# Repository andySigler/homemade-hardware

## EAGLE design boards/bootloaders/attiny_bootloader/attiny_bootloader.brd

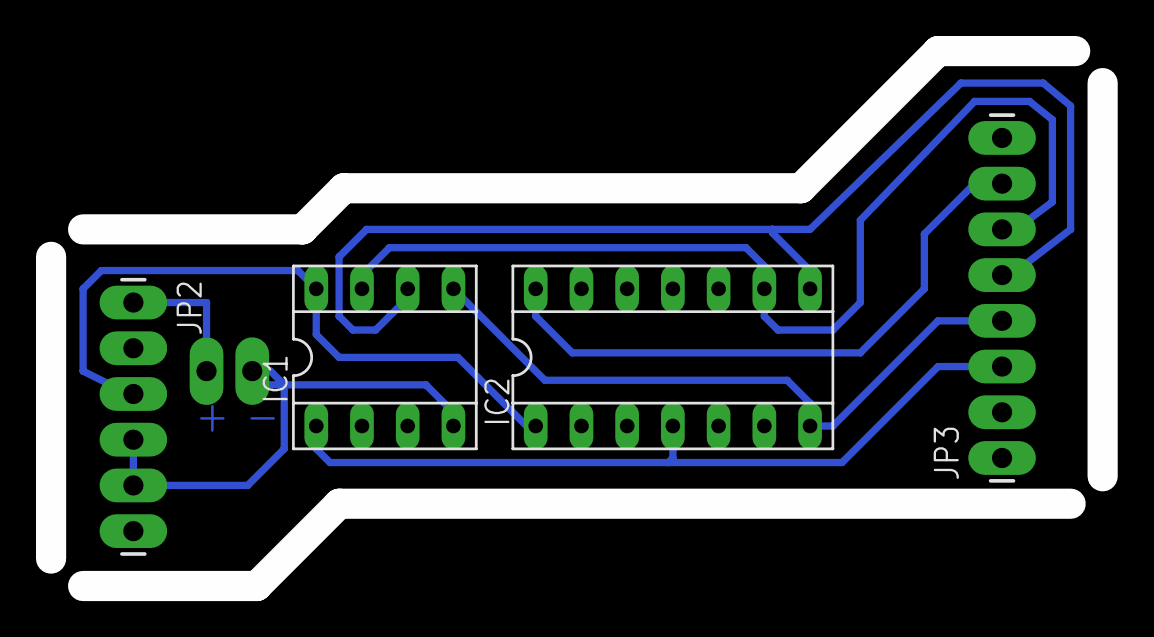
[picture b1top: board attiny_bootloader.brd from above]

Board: 2 copper layers, 58.4 x 29.7 mm, 5 parts (0 on the bottom side), 8 nets.

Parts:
IC1: SOCKET-08
IC2: SOCKET-14
JP1: M02PTH3; 1X02_LONGPADS
JP2: 1X06_LONGPADS
JP3: 1X08_LONGPADS

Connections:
GND: IC1.4, JP1.2, JP2.4, JP2.5
unnamed: IC2.14, JP3.7
unnamed: IC1.1, IC2.4, JP3.3
unnamed: IC1.7, IC2.9, JP3.6
unnamed: IC1.6, IC2.8, JP3.5
unnamed: IC1.5, IC2.7, JP3.4
unnamed: JP1.1, JP2.1
VCC: IC1.8, IC2.1, JP2.3

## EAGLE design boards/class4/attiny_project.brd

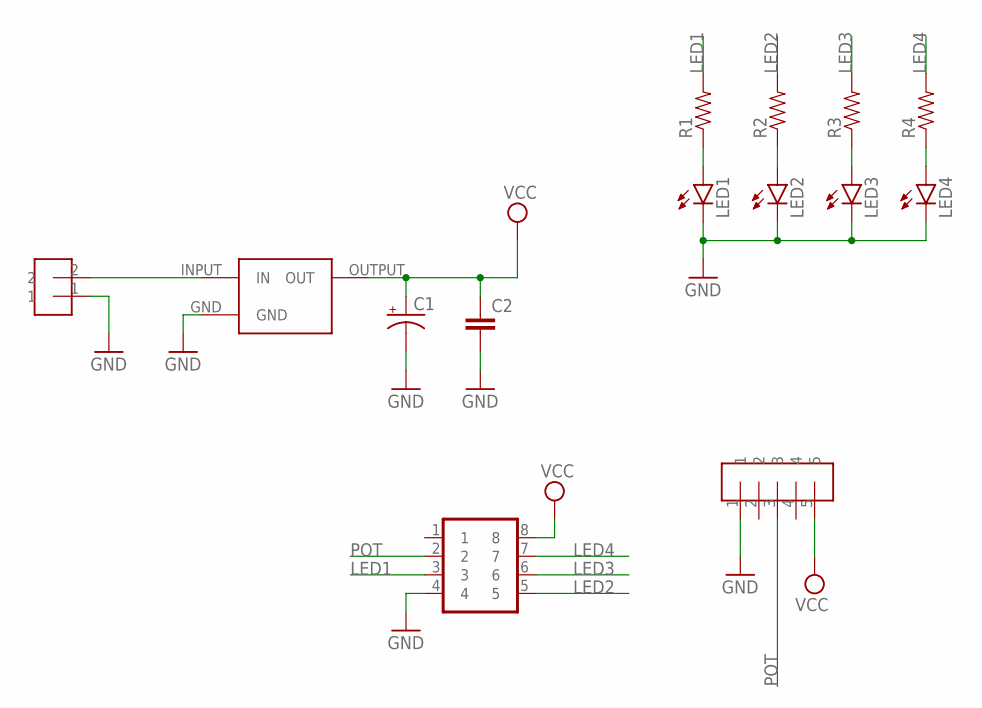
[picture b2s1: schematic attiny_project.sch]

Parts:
C1: CAP_POLPTH2; CPOL-RADIAL-10UF-25V
C2: CAPPTH; CAP-PTH-SMALL
LED1, LED2, LED3, LED4: LED5MM
R1, R2, R3, R4: RESISTORPTH-1/4W; AXIAL-0.4
U$1: SOCKET-8PINDIP; SOCKET-8PIN
U$2: HEADER-5
U$3: REGULATOR5V-MC7805CT; REGULATOR-7805
U$4: HEADER-2

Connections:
GND: C1.2 (-), C2.2, LED1.K (C), LED2.K (C), LED3.K (C), LED4.K (C), U$1.4, U$2.1, U$3.GND, U$4.1
LED1: R1.P$2 (2), U$1.3
LED2: R2.P$2 (2), U$1.5
LED3: R3.P$2 (2), U$1.6
LED4: R4.P$2 (2), U$1.7
unnamed: U$3.INPUT (IN), U$4.2
unnamed: LED1.A, R1.P$1 (1)
unnamed: LED2.A, R2.P$1 (1)
unnamed: LED3.A, R3.P$1 (1)
unnamed: LED4.A, R4.P$1 (1)
POT: U$1.2, U$2.3
VCC: C1.1 (+), C2.1, U$1.8, U$2.5, U$3.OUTPUT (OUT)

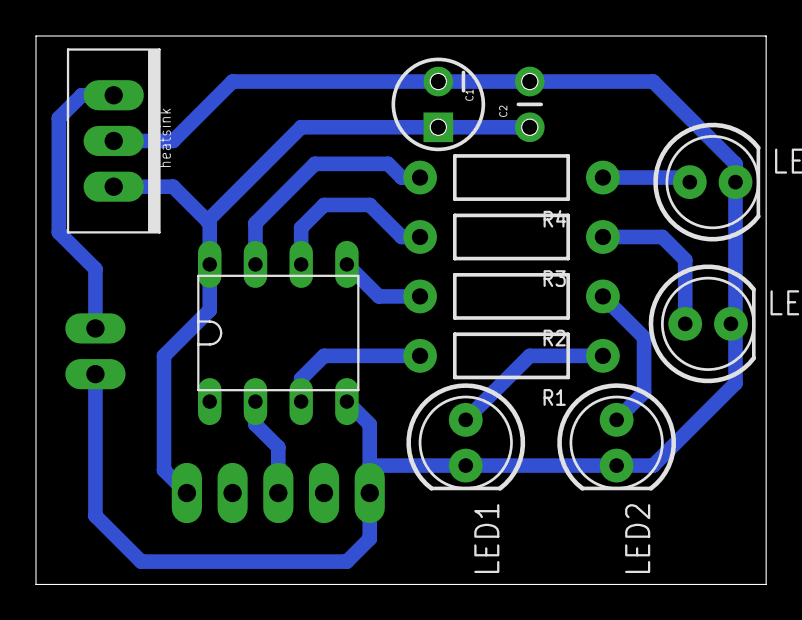
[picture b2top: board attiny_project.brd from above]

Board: 2 copper layers, 40.6 x 30.5 mm, 14 parts (0 on the bottom side), 12 nets.

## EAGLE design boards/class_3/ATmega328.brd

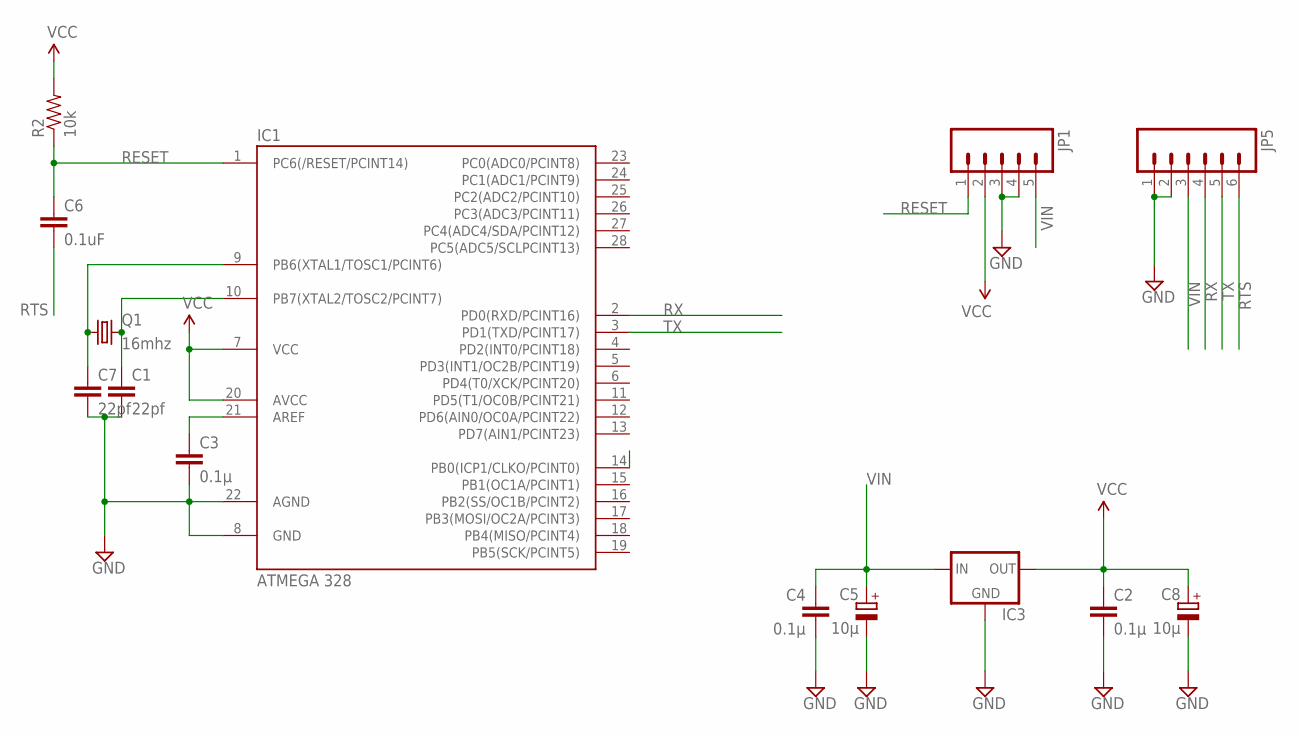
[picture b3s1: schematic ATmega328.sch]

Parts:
C1, C7: 22pf; C025-024X044
C2, C3, C4: 0.1µ; C025-024X044
C5, C8: 10µ; E1,8-4
C6: 0.1uF; CAP-PTH-5MM
IC1: ATMEGA 328; DIL28-3
IC3: V_REG_78XXSIDE; 78XXL
JP1: M05PTH_LONGPADS; 1X05_LONGPADS
JP5: M06NO_SILK; 1X06_NO_SILK
Q1: 16mhz; HC49/S
R2: 10k; 1/6W-RES

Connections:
GND: C1.2, C2.2, C3.2, C4.2, C5.-, C7.2, C8.-, IC1.8 (GND), IC1.22 (AGND), IC3.GND, JP1.3, JP1.4, JP5.1, JP5.2
unnamed: C7.1, IC1.9 (PB6(XTAL1/TOSC1/PCINT6)), Q1.1
unnamed: C3.1, IC1.21 (AREF)
unnamed: C1.1, IC1.10 (PB7(XTAL2/TOSC2/PCINT7)), Q1.2
RESET: C6.1, IC1.1 (PC6(/RESET/PCINT14)), JP1.1, R2.1
RTS: C6.2, JP5.6
RX: IC1.2 (PD0(RXD/PCINT16)), JP5.4
TX: IC1.3 (PD1(TXD/PCINT17)), JP5.5
VCC: C2.1, C8.+, IC1.7 (VCC), IC1.20 (AVCC), IC3.OUT, JP1.2, R2.2
VIN: C4.1, C5.+, IC3.IN, JP1.5, JP5.3

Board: 2 copper layers, 14 parts (0 on the bottom side), 10 nets, no tracks yet.

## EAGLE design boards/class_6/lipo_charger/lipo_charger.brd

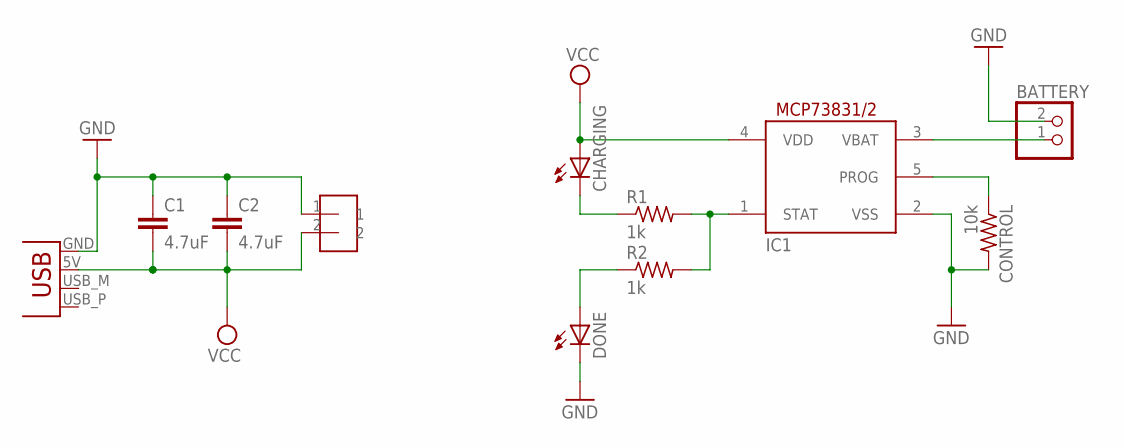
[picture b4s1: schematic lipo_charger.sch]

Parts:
BATTERY: JST_2PIN-SMT-RA; JST-PH-2-SMT-RA
C1, C2: 4.7uF; 0603-CAP
CHARGING: LEDCHIPLED_0603; CHIPLED_0603
CONTROL: 10k; R0603
DONE: LEDCHIPLED_0603; CHIPLED_0603
IC1: MCP73831/OT; SOT23-5L
JP1: USBPCB; USB-A-PCB
R1, R2: 1k; R0603
U$1: HEADER-2

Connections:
GND: BATTERY.2 (1), C1.1, C2.1, CONTROL.2, DONE.C, IC1.2 (VSS), JP1.GND, U$1.1
unnamed: IC1.1 (STAT), R1.2, R2.2
unnamed: CHARGING.C, R1.1
unnamed: DONE.A, R2.1
unnamed: BATTERY.1 (2), IC1.3 (VBAT)
unnamed: CONTROL.1, IC1.5 (PROG)
VCC: C1.2, C2.2, CHARGING.A, IC1.4 (VDD), JP1.5V (VBUS), U$1.2

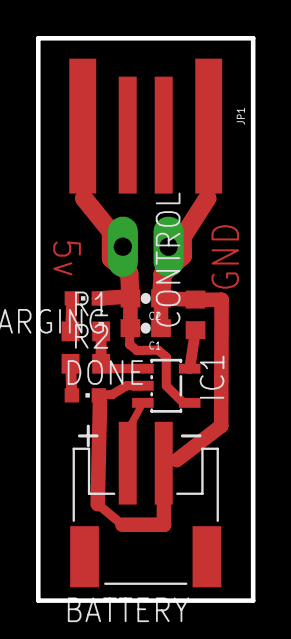
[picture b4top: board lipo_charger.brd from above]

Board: 2 copper layers, 11.9 x 31.2 mm, 11 parts (0 on the bottom side), 7 nets.

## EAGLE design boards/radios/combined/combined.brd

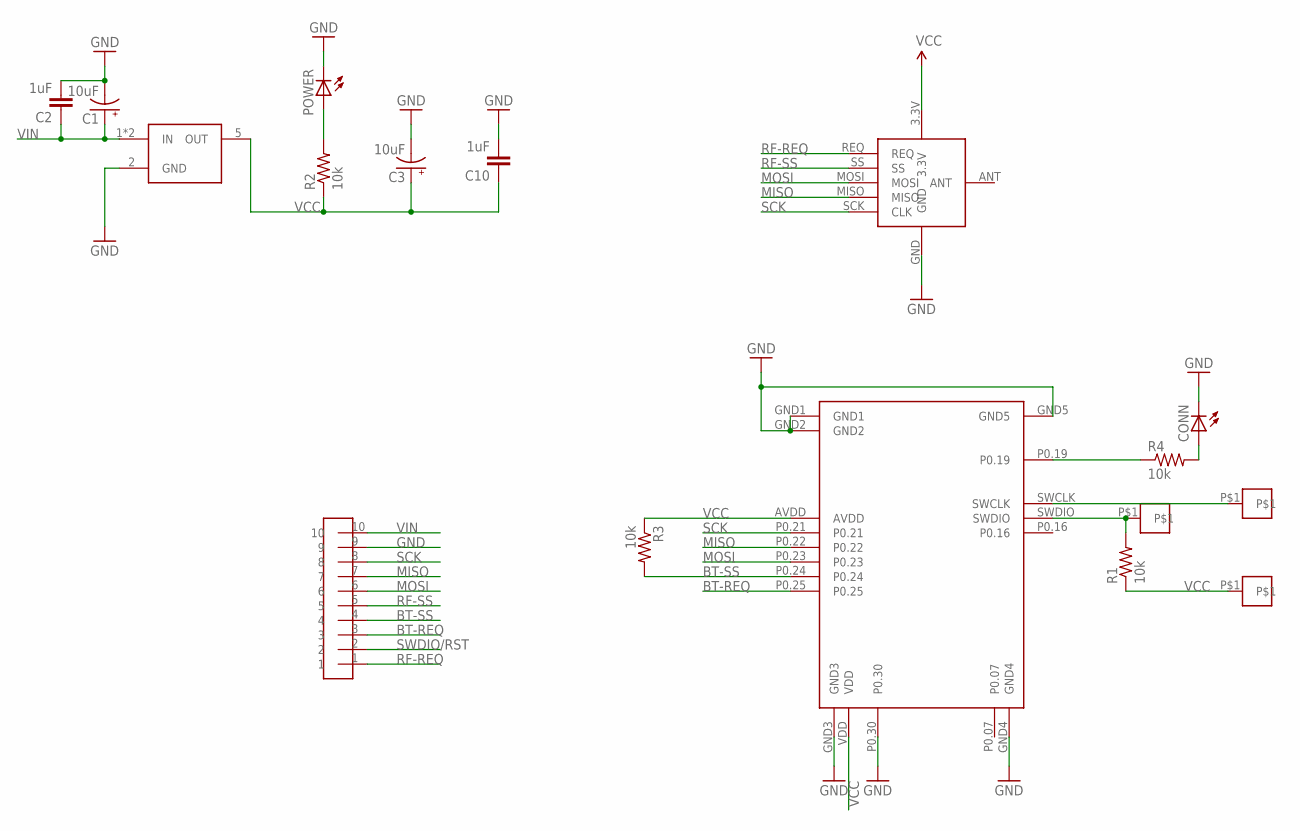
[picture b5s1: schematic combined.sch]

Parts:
C1, C3: 10uF; EIA3216
C2, C10: 1uF; 0603-CAP
CLOCK, CLOCK1: PAD; SMD-ROUND
CONN: LEDCHIP-LED0603; CHIP-LED0603
POWER: LEDCHIP-LED0603; CHIP-LED0603
R1, R3: 10k; 0603-RES
R2, R4: 10k; R0603
U$1: RFM69; S0C-RFM69
U$2: HEADER-10
U$3: REGULATOR3.3V-MIC5205; SOT23-5
U$5: NRF51-MDBT40-SPI; SOC-NRF51-MDBT40-SPI
VCC: PAD; SMD-ROUND

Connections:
BT-REQ: U$2.3, U$5.P0.25
BT-SS: R3.2, U$2.4, U$5.P0.24
GND: C1.C (-), C2.2, C3.C (-), C10.2, CONN.C, POWER.C, U$1.GND, U$2.9, U$3.2 (GND), U$5.GND1, U$5.GND2, U$5.GND3, U$5.GND4, U$5.GND5, U$5.P0.30
MISO: U$1.MISO, U$2.7, U$5.P0.22
MOSI: U$1.MOSI, U$2.6, U$5.P0.23
unnamed: POWER.A, R2.2
unnamed: R4.1, U$5.P0.19
unnamed: CONN.A, R4.2
unnamed: CLOCK.P$1, U$5.SWCLK
RF-REQ: U$1.REQ, U$2.1
RF-SS: U$1.SS, U$2.5
SCK: U$1.SCK (CLK), U$2.8, U$5.P0.21
SWDIO/RST: CLOCK1.P$1, R1.2, U$2.2, U$5.SWDIO
VCC: C3.A (+), C10.1, R1.1, R2.1, R3.1, U$1.3.3V, U$3.5 (OUT), U$5.AVDD, U$5.VDD, VCC.P$1
VIN: C1.A (+), C2.1, U$2.10, U$3.1 (IN), U$3.3 (IN)

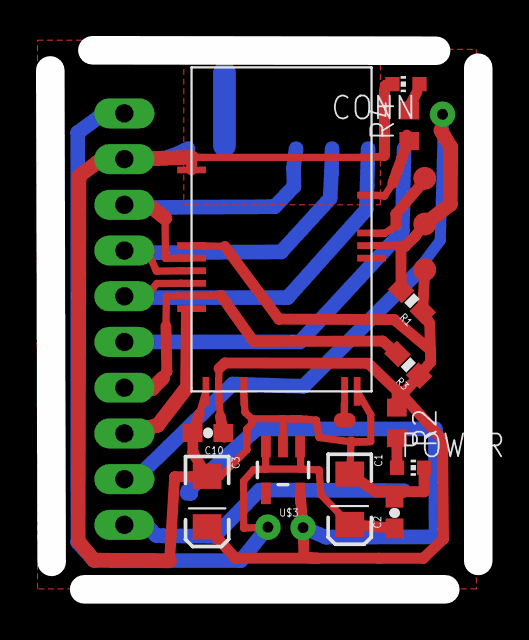
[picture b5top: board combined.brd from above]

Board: 2 copper layers, 23.8 x 29.9 mm, 17 parts (1 on the bottom side), 15 nets.

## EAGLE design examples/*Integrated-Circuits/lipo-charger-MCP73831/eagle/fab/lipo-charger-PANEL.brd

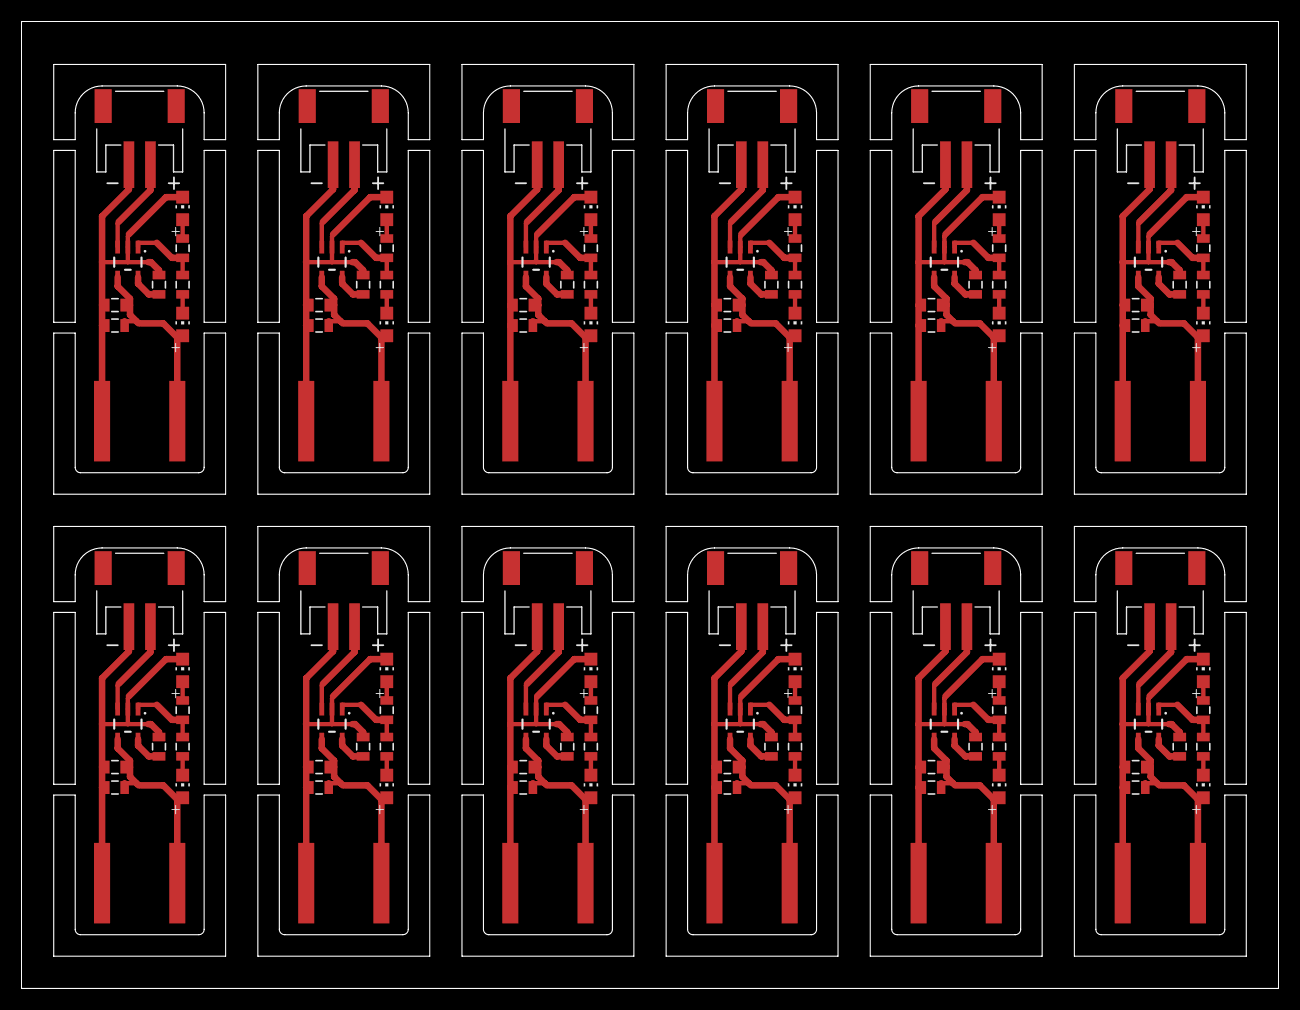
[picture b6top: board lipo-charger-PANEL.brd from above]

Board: 2 copper layers, 117.0 x 90.0 mm, 120 parts (0 on the bottom side), 84 nets.

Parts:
C1, C3, C5, C7, C9, C11, C13, C15, C17, C19, C21, C23: 10uF; 0805
C2, C4, C6, C8, C10, C12, C14, C16, C18, C20, C22, C24: 0.1uF; 0805
IC1, IC2, IC3, IC4, IC5, IC6, IC7, IC8, IC9, IC10, IC11, IC12: IC_LIPO_CHARGER; SOT23-5
LED1, LED3, LED5, LED7, LED9, LED11, LED13, LED15, LED17, LED19, LED21, LED23: Red; CHIP-LED0805
LED2, LED4, LED6, LED8, LED10, LED12, LED14, LED16, LED18, LED20, LED22, LED24: Blue; CHIP-LED0805
R1, R2, R4, R5, R7, R8, R10, R11, R13, R14, R16, R17, R19, R20, R22, R23, R25, R26, R28, R29, R31, R32, R34, R35: 1k; 0805
R3, R6, R9, R12, R15, R18, R21, R24, R27, R30, R33, R36: 10k; 0805
U$1, U$3, U$5, U$7, U$9, U$11, U$13, U$15, U$17, U$19, U$21, U$23: CONN_BATTERY-LIPO-HORIZ; JST-PH-2-SMT-RA
U$2, U$4, U$6, U$8, U$10, U$12, U$14, U$16, U$18, U$20, U$22, U$24: CONN_USB_PCB_POWER; USB-PCB-POWER

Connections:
5V1: C1.1, C2.1, IC1.4, LED1.A, U$2.5V
5V2: C3.1, C4.1, IC2.4, LED3.A, U$4.5V
5V3: C5.1, C6.1, IC3.4, LED5.A, U$6.5V
5V4: C7.1, C8.1, IC4.4, LED7.A, U$8.5V
5V5: C9.1, C10.1, IC5.4, LED9.A, U$10.5V
5V6: C11.1, C12.1, IC6.4, LED11.A, U$12.5V
5V7: C13.1, C14.1, IC7.4, LED13.A, U$14.5V
5V8: C15.1, C16.1, IC8.4, LED15.A, U$16.5V
5V9: C17.1, C18.1, IC9.4, LED17.A, U$18.5V
5V10: C21.1, C22.1, IC11.4, LED21.A, U$22.5V
5V11: C23.1, C24.1, IC12.4, LED23.A, U$24.5V
5V12: C19.1, C20.1, IC10.4, LED19.A, U$20.5V
BATTERY1: IC1.3, U$1.1
BATTERY2: IC2.3, U$3.1
BATTERY3: IC3.3, U$5.1
BATTERY4: IC4.3, U$7.1
BATTERY5: IC5.3, U$9.1
BATTERY6: IC6.3, U$11.1
BATTERY7: IC7.3, U$13.1
BATTERY8: IC8.3, U$15.1
BATTERY9: IC9.3, U$17.1
BATTERY10: IC11.3, U$21.1
BATTERY11: IC12.3, U$23.1
BATTERY12: IC10.3, U$19.1
CURRENT-CONTROL1: IC1.5, R3.2
CURRENT-CONTROL2: IC2.5, R6.2
CURRENT-CONTROL3: IC3.5, R9.2
CURRENT-CONTROL4: IC4.5, R12.2
CURRENT-CONTROL5: IC5.5, R15.2
CURRENT-CONTROL6: IC6.5, R18.2
CURRENT-CONTROL7: IC7.5, R21.2
CURRENT-CONTROL8: IC8.5, R24.2
CURRENT-CONTROL9: IC9.5, R27.2
CURRENT-CONTROL10: IC11.5, R33.2
CURRENT-CONTROL11: IC12.5, R36.2
CURRENT-CONTROL12: IC10.5, R30.2
GND1: C1.2, C2.2, IC1.2, LED2.C, R3.1, U$1.2, U$2.GND
GND2: C3.2, C4.2, IC2.2, LED4.C, R6.1, U$3.2, U$4.GND
GND3: C5.2, C6.2, IC3.2, LED6.C, R9.1, U$5.2, U$6.GND
GND4: C7.2, C8.2, IC4.2, LED8.C, R12.1, U$7.2, U$8.GND
GND5: C9.2, C10.2, IC5.2, LED10.C, R15.1, U$9.2, U$10.GND
GND6: C11.2, C12.2, IC6.2, LED12.C, R18.1, U$11.2, U$12.GND
GND7: C13.2, C14.2, IC7.2, LED14.C, R21.1, U$13.2, U$14.GND
GND8: C15.2, C16.2, IC8.2, LED16.C, R24.1, U$15.2, U$16.GND
GND9: C17.2, C18.2, IC9.2, LED18.C, R27.1, U$17.2, U$18.GND
GND10: C21.2, C22.2, IC11.2, LED22.C, R33.1, U$21.2, U$22.GND
GND11: C23.2, C24.2, IC12.2, LED24.C, R36.1, U$23.2, U$24.GND
GND12: C19.2, C20.2, IC10.2, LED20.C, R30.1, U$19.2, U$20.GND
unnamed: LED1.C, R2.2
unnamed: LED2.A, R1.1
unnamed: LED3.C, R5.2
unnamed: LED4.A, R4.1
unnamed: LED5.C, R8.2
unnamed: LED6.A, R7.1
unnamed: LED7.C, R11.2
unnamed: LED8.A, R10.1
unnamed: LED9.C, R14.2
unnamed: LED10.A, R13.1
unnamed: LED11.C, R17.2
unnamed: LED12.A, R16.1
unnamed: LED13.C, R20.2
unnamed: LED14.A, R19.1
unnamed: LED15.C, R23.2
unnamed: LED16.A, R22.1
unnamed: LED17.C, R26.2
unnamed: LED18.A, R25.1
unnamed: LED19.C, R29.2
unnamed: LED20.A, R28.1
unnamed: LED21.C, R32.2
unnamed: LED22.A, R31.1
unnamed: LED23.C, R35.2
unnamed: LED24.A, R34.1
STATUS1: IC1.1, R1.2, R2.1
STATUS2: IC2.1, R4.2, R5.1
STATUS3: IC3.1, R7.2, R8.1
STATUS4: IC4.1, R10.2, R11.1
STATUS5: IC5.1, R13.2, R14.1
STATUS6: IC6.1, R16.2, R17.1
STATUS7: IC7.1, R19.2, R20.1
STATUS8: IC8.1, R22.2, R23.1
STATUS9: IC9.1, R25.2, R26.1
STATUS10: IC11.1, R31.2, R32.1
STATUS11: IC12.1, R34.2, R35.1
STATUS12: IC10.1, R28.2, R29.1

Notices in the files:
parts and their libraries:
SparkFun-Connectors: Licensing: Creative Commons ShareAlike 4.0 International - https://creativecommons.org/licenses/by-sa/4.0
SparkFun-Connectors: Licensing: CC v3.0 Share-Alike You are welcome to use this library for commercial purposes.
